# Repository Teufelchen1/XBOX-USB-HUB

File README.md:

# XBOX-USB-HUB
Collection of information and homemade schematics of the XBOX Rev 1.0 USB PCB

| Label  |Value   |CLabel   |State   |Function|
|--------|--------|---------|--------|--------|
|R1|0|R1|Ok|In series DM0|
|R2|0|R2|Ok|In series DP0|
|R3|700|R3|Value guessed|Pull-up DP0|
|R4|||Unkown||
|R5|1.5k|R5|Value from DS|between IC & crystal|
|R6|15k|R6|Value guessed|Pull-down DM1|
|R7|15k|R7|Value guessed|Pull-down DP1|
|R8|36|R8|Value guessed|Termination of DM1|
|R9|36|R9|Value guessed|Termination of DP4|
|R10|36|R10|Value guessed|Termination of DP1|
|R11|35|R11|Value guessed|Termination of DM4|
|R12|15k|R12|Value guessed|Pull-down DP4|
|R13|15k|R13|Value guessed|Pull-down DM4|
|R14|36|R14|Value guessed|Termination of DM2|
|R15|15k|R15|Value guessed|Pull-down DM2|
|R16|15k|R16|Value guessed|Pull-down DP2|
|R17|36|R17|Value guessed|Termination of DP2|
|R18|36|R18|Value guessed|Termination of DP3|
|R19|36|R19|Value guessed|Termination of DM3|
|R20|15k|R20|Value guessed|Pull-down DM3|
|R21|15k|R21|Value guessed|Pull-down DP3|
|C21||C21|intended|Stability 5V-GND controler 3/4|
|C26||C26|intended|Stability 5V-GND controler 3/4|
|C4|||Unpopulated||
|C3|||Unpopulated||
|C6|||Unpopulated||
|C9|||Unpopulated||
|C10|||Unpopulated||
|C14|||Unpopulated||
|C15|||Unpopulated||
|C18|||Missing|Stability 3.3V-GND|
|C5|||Missing|Stability 3.3V-GND|
|C2|||Missing|Stability 3.3V-GND|
|C19|||Missing|Stability 3.3V-GND|
|C20|||Missing|Stability 3.3V-GND|
|C7|27pF|C7|Value from DS|crystal|
|C8|27pF|C8|Value from DS|crystal|
|C24|||Missing|GND-C24-L3-3.3V|
|C25|||Missing|GND-C25-L3-3.3V|
|C11|||Missing|GND-C11-3.3V|
|C12|||Unpopulated||
|C13|||Unpopulated||
|C16|||Unpopulated||
|C17|||Unpopulated||
|C23||C23|intended|Stability 5V-GND controler 1/2|
|C22||C22|intended|Stability 5V-GND controler 1/2|
|C27|||Missing||
|L7||L7|intended|In series 5V|
|L8||L8|intended|In series 5V|
|L2|||Missing|Common mode chokes|
|L6|||Missing|Common mode chokes|
|L1|||Missing||
|L9|||Missing|Common mode chokes|
|L10|||Missing|Common mode chokes|
|L4||L4|intended|In series 5V|
|L5||L5|intended|In series 5V|
|P1|H JST 12|P1|Ok|Controler 3 & 4|
|P3|2x6 male|P3|Ok|Host USB, Yellow 1 & 2|
|P2|H JST 12|P2|Ok|Controler 1 & 2|
|P4|2x6 male|P4|Ok|Yellow 3 & 4|
|Y1|6MHz|Y1|Ok|crystal|
|U2|TUSB2046B|U2|Ok|Main IC|

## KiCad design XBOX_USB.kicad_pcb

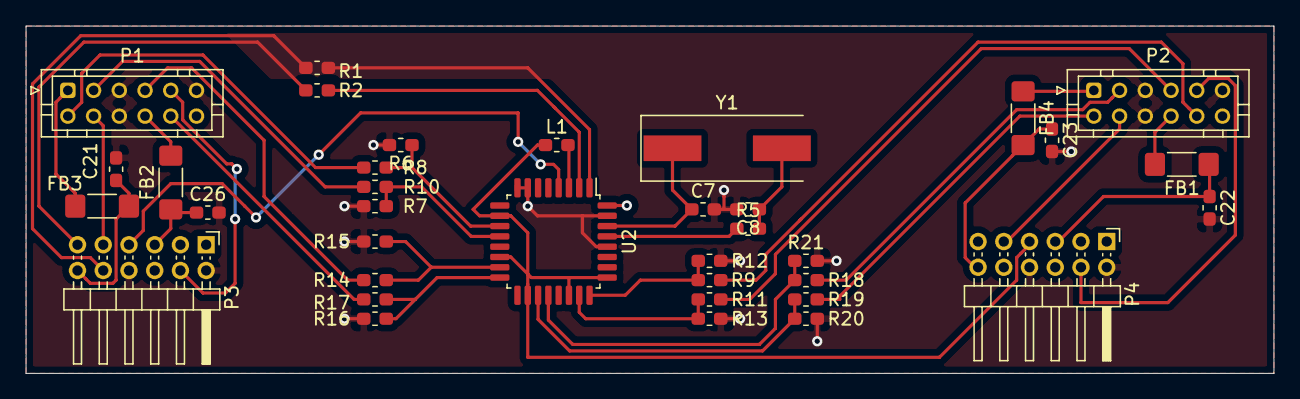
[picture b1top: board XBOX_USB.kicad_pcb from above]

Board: 2 copper layers, 97.0 x 27.0 mm, 36 parts (0 on the bottom side), 39 nets.

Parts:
C7, C8: 27pF; C_0603_1608Metric_Pad1.05x0.95mm_HandSolder
C21, C22, C23, C26: 100µF; C_0603_1608Metric_Pad1.05x0.95mm_HandSolder
FB1, FB2, FB3, FB4: Ferrite_Bead_Small; L_1806_4516Metric_Pad1.57x1.80mm_HandSolder
L1: L_Small; L_0603_1608Metric_Pad1.05x0.95mm_HandSolder
P1, P2: H JST 12; JST_PHD_B12B-PHDSS_2x06_P2.00mm_Vertical
P3, P4: Conn_02x06_Odd_Even; PinHeader_2x06_P2.00mm_Horizontal
R1, R2: 0; R_0603_1608Metric_Pad1.05x0.95mm_HandSolder
R5: 1.5k; R_0603_1608Metric_Pad1.05x0.95mm_HandSolder
R6, R7, R12, R13, R15, R16, R20, R21: 15k; R_0603_1608Metric_Pad1.05x0.95mm_HandSolder
R8, R9, R10, R11, R14, R17, R18, R19: 36; R_0603_1608Metric_Pad1.05x0.95mm_HandSolder
U2: TUSB2046; LQFP-32_7x7mm_P0.8mm
Y1: 6.0Mhz; Crystal_SMD_HC49-SD

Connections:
+3V3: L1.1, P4.7, U2.10, U2.14, U2.18, U2.22, U2.25
/5V1: FB3.1, P1.1
/5V2: FB2.2, P1.8
/5V3: FB4.1, P2.1
/5V4: FB1.2, P2.8
/DM0Host: P3.11, R2.2
/DM1: P1.2, R8.1
/DM2: P1.7, R14.1
/DM3: P2.2, R19.1
/DM4: P2.7, R11.1
/DP0Host: P3.10, R1.2
/DP1: P1.3, R10.1
/DP2: P1.10, R17.1
/DP3: P2.3, R18.1
/DP4: P2.10, R9.1
/PIN11: R6.1, R8.2, U2.11
/PIN12: R7.2, R10.2, U2.12
/PIN15: R14.2, R15.1, U2.15
/PIN16: R16.1, R17.2, U2.16
/PIN19: R19.2, R20.1, U2.19
/PIN20: R18.2, R21.1, U2.20
/PIN23: R11.2, R13.1, U2.23
/PIN24: R9.2, R12.1, U2.24
/RESET: P3.7, U2.4
/XTAL1: C7.1, U2.30, Y1.1
/XTAL2: R5.1, U2.29
/Yellow1: P1.4, P3.9
/Yellow2: P1.9, P3.4
/Yellow3: P2.4, P4.9
/Yellow4: P2.9, P4.4
GND: C7.2, C8.2, C21.2, C22.2, C23.2, C26.2, P1.5, P1.6, P1.11, P2.5, P2.6, P2.11, P3.2, P3.8, P4.2, P4.8, R6.2, R7.1, R12.2, R13.2, R15.2, R16.2, R20.2, R21.2, U2.7, U2.8, U2.28, U2.31
unnamed: C8.1, R5.2, Y1.2
unnamed: C21.1, FB3.2, P3.12
unnamed: C22.1, FB1.1, P4.5
unnamed: C23.1, FB4.2, P4.12
unnamed: C26.1, FB2.1, P3.5
unnamed: L1.2, U2.3
unnamed: R1.1, U2.1
unnamed: R2.1, U2.2

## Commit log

2019-10-19 adding KiCad images
2019-10-26 doc(readme): Addind a list of all components
2019-10-26 doc(readme): adding connector names to list
